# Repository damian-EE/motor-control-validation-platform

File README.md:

# Custom PCB Motor Control & Validation Platform

A 2-layer KiCad carrier PCB for a small motor test platform (a 12 V DC gear motor with a Hall encoder), plus the breadboard prototype used to validate the circuit. The prototype drives the motor from an Arduino through an H-bridge, measures speed and supply current while it runs, and logs the data to CSV with a Python script. The PCB replaces the breadboard wiring.

## What it does

- Drives a 12 V gear motor with PWM speed and direction control (DRV8871 H-bridge).
- Measures motor speed from the encoder (interrupt-based pulse counting).
- Measures supply voltage and current with an INA219 sensor, averaging many readings per interval because the PWM chops the supply current.
- Streams `time_ms,pwm,rpm,current_mA,voltage_V` every 500 ms over USB serial.
- Runs an automatic PWM sweep, logs it to CSV, and produces time-series, response and run-to-run repeatability plots.

## System overview

```mermaid
flowchart LR
    PSU["12 V supply"] --> INA["INA219<br/>current / voltage"]
    INA --> DRV["DRV8871<br/>H-bridge"]
    DRV --> MOT["12 V gear motor<br/>+ Hall encoder"]
    ARD["Arduino Uno R3"] -- "D9 / D10 PWM" --> DRV
    MOT -- "encoder A (D2)" --> ARD
    INA -- "I2C (A4 / A5)" --> ARD
    ARD -- "USB serial, 9600 baud" --> PC["Python logger<br/>CSV + plots"]
```

**Hardware used**

| Part | Notes |
|---|---|
| Arduino Uno R3 | Motor control, encoder counting, sensor readout |
| DRV8871 breakout | H-bridge, PWM on IN1 (D9) / IN2 (D10) |
| INA219 breakout | High-side current/voltage sensing, I2C |
| 12 V DC gear motor with Hall encoder (25GA370H type) | 45:1 gearbox, 12 pulses/rev on the encoder, 540 pulses per output revolution |
| 12 V supply | Motor and driver |

## Pinout

| Arduino pin | Signal | Used for |
|---|---|---|
| D9 | PWM_IN1 | DRV8871 IN1 (forward) |
| D10 | PWM_IN2 | DRV8871 IN2 (reverse) |
| D2 | ENC_A | Encoder channel A, rising-edge interrupt |
| D3 | ENC_B | Wired to the board, not read by the current firmware |
| A4 / A5 | SDA / SCL | INA219 |
| 5V / GND | | Encoder and INA219 supply, common ground |

The INA219 sits in series on the high side: supply + goes to VIN+, VIN- goes to the DRV8871 VM pin.

## Repository layout

```
firmware/
  motor_controller/      Final Arduino sketch (control + encoder + INA219)
  i2c_scanner/           Utility to confirm the INA219 is detected
  development/           Earlier steps: motor control only, then + encoder RPM
python_logger/
  motor_logger.py        Serial logger and automatic PWM sweep
  plot_results.py        Plots and steady-state table for one run
  compare_runs.py        Overlay and repeatability table for several runs
hardware/
  kicad/                 KiCad 10 project (schematic + PCB)
  gerbers/               Gerber and drill files (also zipped)
  schematic.pdf          Schematic
  bom.csv                Bill of materials
test_results/            Raw CSVs and steady-state summaries
media/                   Plots and board images
```

## How to run it

**1. Firmware.** In the Arduino IDE install the *Adafruit INA219* library (Library Manager), open `firmware/motor_controller/motor_controller.ino`, select the Uno and upload. If the Serial Monitor reports `Failed to find INA219 chip`, upload `firmware/i2c_scanner` to check the wiring (the INA219 normally shows up at `0x40`). Close the Serial Monitor before using the logger, since only one program can hold the port.

**2. Python setup.** Run all Python commands from the repository root so the outputs land in `test_results/` and `media/`.

```
pip install -r python_logger/requirements.txt
python python_logger/motor_logger.py --list     # find the serial port
```

**3. Run a sweep.** This steps through PWM 60, 100, 140, 180, 220, 255, then back down through 180, 100, 0, holding each level for 12 s (about 108 s total) and writing `test_results/run_<timestamp>.csv`:

```
python python_logger/motor_logger.py --port COM3 --sweep --hold 12
```

`python python_logger/motor_logger.py --simulate` runs the whole pipeline with a synthetic motor and no hardware. Simulated output is only for testing the software and is not real data.

**4. Plot.**

```
python python_logger/plot_results.py test_results/run_20261022_031935.csv
python python_logger/compare_runs.py test_results/run_20261022_030916.csv test_results/run_20261022_031231.csv test_results/run_20261022_031935.csv
```

## Results

All results are **no-load** (the motor shaft was not loaded) on a 12 V supply, from three full sweeps on 2026-10-22. Each value is the mean over the second half of a 12 s hold, so the settling transient is excluded.

Steady-state speed on the ramp up, three runs:

| PWM | Run 1 (cold start) | Run 2 | Run 3 | Runs 2-3 differ by |
|---|---|---|---|---|
| 60 | 35.96 RPM | 45.03 | 45.80 | 1.7 % |
| 100 | 79.81 | 86.03 | 85.97 | 0.1 % |
| 140 | 104.12 | 108.62 | 108.49 | 0.1 % |
| 180 | 116.17 | 118.13 | 117.92 | 0.2 % |
| 220 | 124.00 | 125.22 | 124.95 | 0.2 % |
| 255 | 135.02 | 135.64 | 135.34 | 0.2 % |

Supply current at full PWM was about 58 mA (roughly 0.72 W electrical input) in the two warm runs and 61 mA in the cold run, and about 0.05 mA with the motor stopped. Bus voltage stayed between 12.45 V and 12.53 V in all three runs.

Time series of the third run:

Steady-state response of the third run (ramp up solid, ramp down dashed):

Raw data and per-run summaries are in [`test_results/`](test_results/), and the three-run comparison is in [`media/repeatability_summary.csv`](media/repeatability_summary.csv).

### Notes and limitations

- **Run 1 is a cold start.** The gearbox was cold, so at the same PWM it ran slower and drew roughly 5-11 % more current than runs 2 and 3. Runs 2 and 3 agree to within 0.3 % at PWM 100-255. The speed also creeps up slightly during a hold, which is consistent with warm-up.
- **The up/down difference is not cleanly separable from warm-up.** At PWM 100 the ramp-down speed is higher than the ramp-up speed (2.9 % in run 2), but because the motor is warmer by then this is not evidence of true hysteresis.
- **Low PWM is the least repeatable region.** Near PWM 60 the motor is close to the point where friction dominates, so run-to-run differences are largest there.
- **Speed resolution is about 0.22 RPM.** One encoder pulse in a 500 ms window is 1/540 of a revolution.
- **No load, no torque measurement.** Only electrical input power was measured, so this data does not give efficiency or torque.
- **Direction is not sensed.** Only encoder channel A is counted.
- **Discarded runs.** Earlier attempts were excluded and not included: two runs where the logger saved no data or the supply connection dropped out, and one run taken with a loose 12 V connection (bus voltage sagging to 11.6 V, with a dip to 10 V). The connection was fixed before the three runs above.

## PCB

A 80 x 60 mm, 2-layer carrier board (KiCad 10.0.6) that connects the Arduino, the DRV8871 and INA219 modules, the power input and the motor/encoder connector through headers instead of breadboard wires.

- Signal traces on the top layer, with vias to the bottom layer where needed, and a ground zone on the bottom layer.
- Two net classes: default signals (0.4 mm tracks) and a power class (1.0 mm tracks) for the 12 V and motor-output nets.
- Six through-hole test points: +5V, GND, +12V_MOTOR, ENC_A, ENC_B, PWM_IN1.
- Two M3 mounting holes.
- Design rule check was clean (no violations, warnings or unconnected items) at the time of the Gerber export.

Files: [`hardware/schematic.pdf`](hardware/schematic.pdf), [`hardware/bom.csv`](hardware/bom.csv), [`hardware/gerbers/`](hardware/gerbers/), [`hardware/kicad/`](hardware/kicad/).

### Status

The board is **designed and passes DRC, but it has not been fabricated or tested**. All measurements above were taken on a breadboard prototype with the same circuit. Before ordering the board, check that the socket pin order on J4 (INA219) and J5 (DRV8871) matches the actual breakout modules in use, since module pin orders vary between vendors.

## Project scope

The focus of this project is PCB design and hardware validation: the KiCad schematic and board, the breadboard prototype of the circuit, and the test runs and data shown above.

## License

MIT, see [LICENSE](LICENSE).

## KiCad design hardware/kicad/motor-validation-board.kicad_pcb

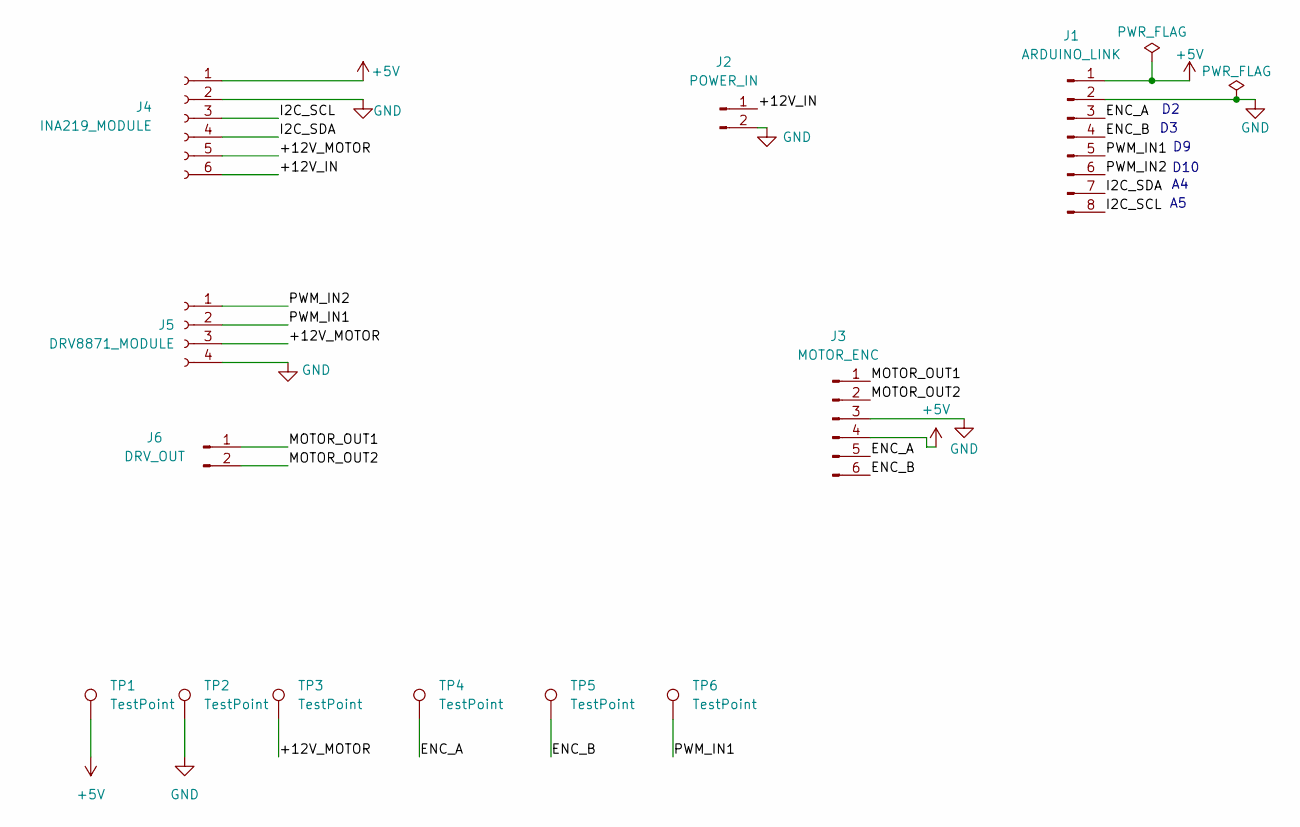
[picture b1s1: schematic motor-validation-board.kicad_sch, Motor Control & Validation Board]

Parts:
J1: ARDUINO_LINK; PinHeader_1x08_P2.54mm_Vertical
J2: POWER_IN; TerminalBlock_Phoenix_MKDS-1,5-2-5.08_1x02_P5.08mm_Horizont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
J3: MOTOR_ENC; PinHeader_1x06_P2.54mm_Vertical
J4: INA219_MODULE; PinSocket_1x06_P2.54mm_Vertical
J5: DRV8871_MODULE; PinSocket_1x04_P2.54mm_Vertical
J6: DRV_OUT; PinHeader_1x02_P2.54mm_Vertical
TP1, TP2, TP3, TP4, TP5, TP6: TestPoint; TestPoint_THTPad_D2.0mm_Drill1.0mm

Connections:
+5V: J1.1, J3.4, J4.1, TP1.1 (1_1)
/+12V_IN: J2.1, J4.6
/+12V_MOTOR: J4.5, J5.3, TP3.1 (1_1)
/ENC_A: J1.3, J3.5, TP4.1 (1_1)
/ENC_B: J1.4, J3.6, TP5.1 (1_1)
/I2C_SCL: J1.8, J4.3
/I2C_SDA: J1.7, J4.4
/MOTOR_OUT1: J3.1, J6.1
/MOTOR_OUT2: J3.2, J6.2
/PWM_IN1: J1.5, J5.2, TP6.1 (1_1)
/PWM_IN2: J1.6, J5.1
GND: J1.2, J2.2, J3.3, J4.2, J5.4, TP2.1 (1_1)

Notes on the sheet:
D10

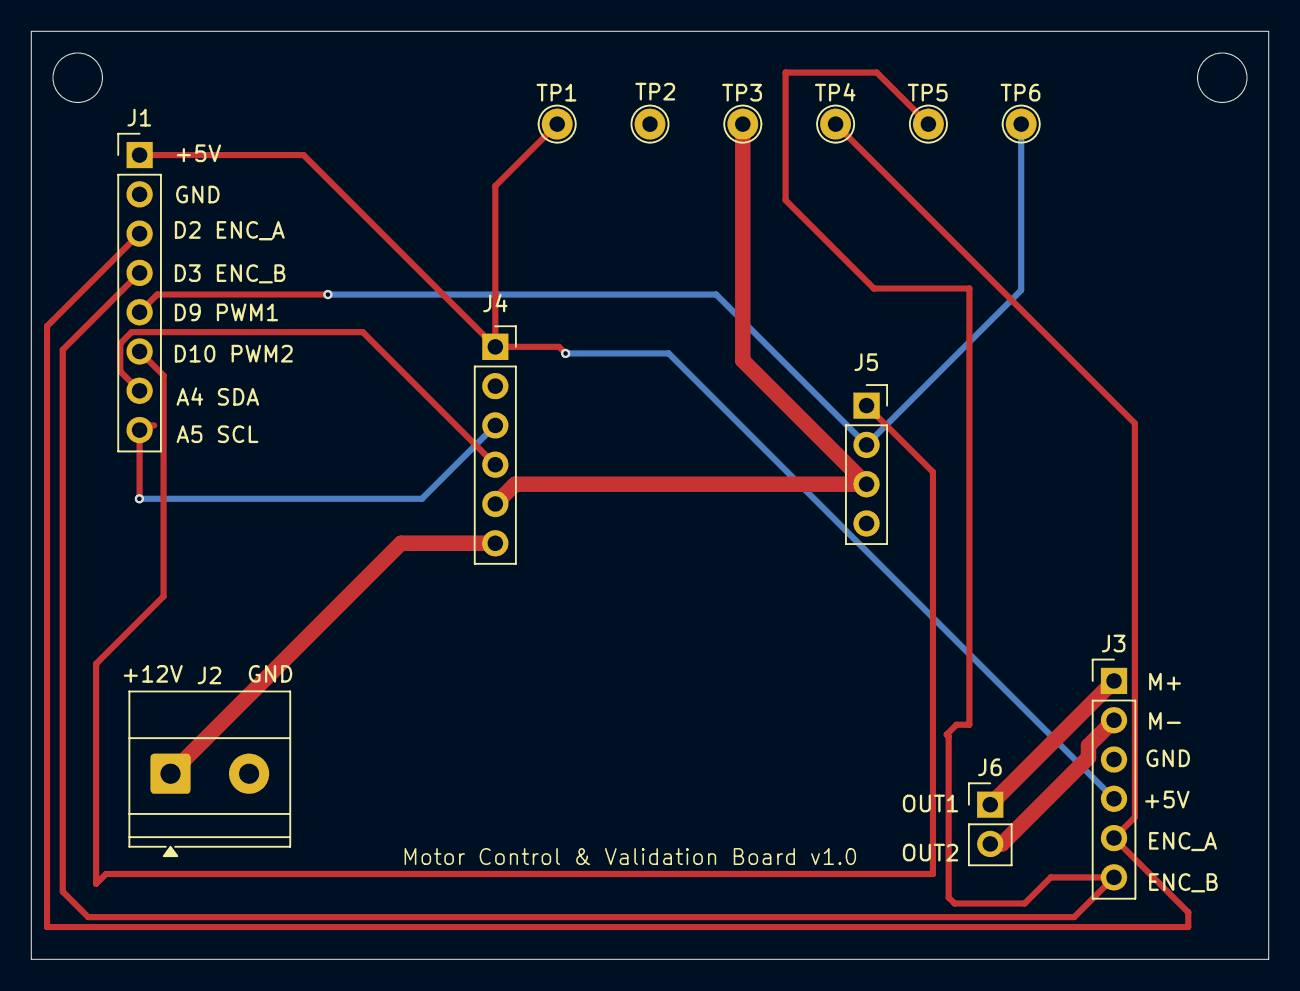
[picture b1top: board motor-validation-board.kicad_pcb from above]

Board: 2 copper layers, 80.0 x 60.0 mm, 12 parts (0 on the bottom side), 12 nets.
